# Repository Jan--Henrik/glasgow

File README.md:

# Glasgow Debug Tool

# This is not the official revC2 branch, I just added USB-C for myself!

**Want one? [Subscribe here](https://mailchi.mp/44980ff6f0ab/glasgow-announcements).**

**Let's chat! Our IRC channel is [#glasgow at freenode.net](https://webchat.freenode.net/?channels=glasgow); our discussion forum is [glasgow.whitequark.org](https://glasgow.whitequark.org/).**

**Important note: if you are looking to assemble boards yourself, use only revC1.**

## What is Glasgow?

Glasgow is a tool for exploring digital interfaces, aimed at embedded developers, reverse engineers, digital archivists, electronics hobbyists, and everyone else who wants to communicate to a wide selection of digital devices with high reliability and minimum hassle. It can be attached to most devices without additional active or passive components, and includes extensive protection from unexpected conditions and operator error.

The Glasgow hardware can support many digital interfaces because it uses reconfigurable logic. Instead of only offering a small selection of standard hardware supported interfaces, it uses an FPGA to adapt on the fly to the task at hand without compromising on performance or reliability, even for unusual, custom or obsolete interfaces.

The Glasgow software is a set of building blocks designed to eliminate incidental complexity. Each interface is packaged into a self-contained *applet* that can be used directly from the command line, or reused as a part of a more complex system. Using Glasgow does not require any programming knowledge, although it becomes much more powerful if you know a bit of Python.

## What can I do with Glasgow?

Some of the tasks Glasgow can do well are:

  * communicate via UART,
    * automatically determine and follow the baud rate of device under test,
  * initiate transactions via SPI or I²C,
  * read and write 24-series EEPROMs,
  * read and write 25-series Flash memories,
    * determine memory parameters via SFDP,
  * read and write ONFI-compatible Flash memories,
    * determine memory parameters via ONFI parameter page,
  * program and verify AVR microcontrollers with SPI interface,
  * automatically determine unknown JTAG pinout,
  * play back JTAG SVF files,
  * debug ARC processors via JTAG,
  * debug some MIPS processors via EJTAG,
  * program and verify XC9500XL CPLDs via JTAG,
  * synthesize sound using a Yamaha OPLx/OPM chip and play it in real time on a webpage,
  * read raw modulated data from 5.25"/3.5" floppy drives,
  * ... and more!

Everything above can be done with only a Glasgow revC board, some wires, and depending on the device under test, external power.

## How does using Glasgow look like?

Watch a typical command-line workflow in this screencast:

## What hardware does Glasgow use?

The Glasgow hardware evolves over time, with each major milestone called a "revision". Although all revisions are, and will always be supported with the same software, they vary significantly in their capabilities, and the chosen revision will limit the possible tasks.

Glasgow boards use a version in the `revXN` format, where `X` is a revision letter (increased on major design changes) and `N` is a stepping number (increased on any layout or component changes). For example, `revC0` is the first stepping of revision C.

### revA/revB

Revisions A and B have not been produced in significant amounts, contain major design issues, and are therefore mostly of historical interest. Nevertheless, everyone who has one of the revA/revB boards can keep using them—forever.

### revC

Revision C is the latest revision and is being prepared for mass production. It provides 16 I/O pins with a maximum frequency of approx. 100 MHz\*, independent direction control and independent programmable pull-up/pull-down resistors. The I/O pins are grouped into two I/O ports that can use any voltage from 1.8 V to 5 V, sense and monitor I/O voltage of the device under test, as well as provide up to 150 mA of power. The board uses USB 2 for power, configuration, and communication, achieving up to 336 Mbps (42 MB/s) of sustained combined throughput.

<sub>\* Maximum frequency achievable in practice depends on many factors and will vary greatly with specific interface and applet design. 24 MHz non-DDR can be achieved for most interfaces with minimal effort.</sub>

## What software does Glasgow use?

Glasgow is written entirely in Python 3. The interface logic that runs on the FPGA is described using [Migen](https://m-labs.hk/migen/), which is a Python-based domain specific language. The supporting code that runs on the host PC is written in Python with [asyncio](https://docs.python.org/3/library/asyncio.html). This way, the logic on the FPGA can be assembled on demand for any requested configuration, keeping it as fast and compact as possible, and code can be shared between gateware and software, removing the need to add error-prone "glue" boilerplate.

Glasgow would not be possible without the [open-source iCE40 FPGA toolchain](http://www.clifford.at/icestorm/), which is not only very reliable but also extremely fast. It is so fast that FPGA bitstreams are not cached (beyond not rebuilding the bitstream already on the device), as it only takes a few seconds to build one from scratch for something like an UART. When developing a new applet it is rarely necessary to wait for the toolchain.

Implementing reliable, high-performance USB communication is not trivial—packetization, buffering, and USB quirks add up. Glasgow abstracts away USB: on the FPGA, the applet gateware writes to or reads from a FIFO, and on the host, applet software writes to or reads from a socket-like interface. Idiomatic Python code can communicate at maximum USB 2 bulk bandwidth on a modern PC without additional effort. Moreover, when a future Glasgow revision will use Ethernet in addition to USB, no changes to applet code will be required.

Debugging new applets can be hard, especially if bidirectional buses are involved. Glasgow provides a built-in cycle-accurate logic analyzer that can relate the I/O pin level and direction changes to commands and responses received and sent by the applet. The logic analyzer compresses waveforms and can pause the applet if its buffer is about to overflow.

## How do I use Glasgow?

### ... with Linux?

**Multiple people have reported various issues with the installation instructions below. If any part of these does not work, please file it as a bug, so that the experience can be made more smooth for everyone.**

You will need git, build tools, sdcc, Python 3.7 (or a newer version, in which case replace `3.7` with that version below). On a Debian or Ubuntu system these can be installed with:

    apt-get install --no-install-recommends git build-essential sdcc \
      python3.7 python3-setuptools python3-libusb1 python3-aiohttp python3-bitarray python3-crcmod

You will also need Yosys and nextpnr-ice40, both from the master branch. Follow the setup instructions for [Yosys](https://github.com/yosysHQ/yosys/#setup) and [nextpnr](https://github.com/YosysHQ/nextpnr/#nextpnr-ice40).

Obtain the source code:

    git clone https://github.com/GlasgowEmbedded/glasgow
    cd glasgow
    git submodule update --init vendor/libfx2

Configure your system to allow unprivileged access (for anyone in the `plugdev` group) to the Glasgow hardware:

    sudo cp config/99-glasgow.rules /etc/udev/rules.d

Install the dependencies and the binaries for the current user:

    cd software
    python3.7 setup.py develop --user

The binaries are placed in `$HOME/.local/bin`, so be sure to add that directory to the `PATH` environment variable; after this, you can run `glasgow` from a terminal. Instead of adjusting `PATH` it is also possible to use `python3.7 -m glasgow.cli`.

When you connect your board for the first time after assembly you have to flash it initially, run the following command.

    glasgow factory --rev {A0|B0|C0|C1}

To update the source code, do:

    cd glasgow
    git pull
    cd software
    python3.7 setup.py build_ext

### ... with Windows?

Although first-class Windows support is an important goal and Glasgow already works on Windows, the installation process is not yet ready.

## Who made Glasgow?

  * [@whitequark](https://github.com/whitequark) came up with the design, coordinates the project and implements most of gateware and software;
  * [@awygle](https://github.com/awygle) designed the power/analog port circuitry and helped with layout of revB;
  * [@marcan](https://github.com/marcan) improved almost every aspect of hardware for revC;
  * [@esden](https://github.com/esden) is handling batch manufacturing;
  * [@smunaut](https://github.com/smunaut) provided advice crucial for stability and performance of USB communication;
  * [@electronic_eel](https://github.com/electronic_eel) designed the test jig and advanced protection circuitry;
  * ... and many [other people](https://github.com/GlasgowEmbedded/Glasgow/graphs/contributors).

## License

Glasgow is distributed under the terms of both 0-clause BSD license as well as Apache 2.0 license.

See [LICENSE-0BSD](LICENSE-0BSD.txt) and [LICENSE-Apache-2.0.txt](LICENSE-Apache-2.0.txt) for details.

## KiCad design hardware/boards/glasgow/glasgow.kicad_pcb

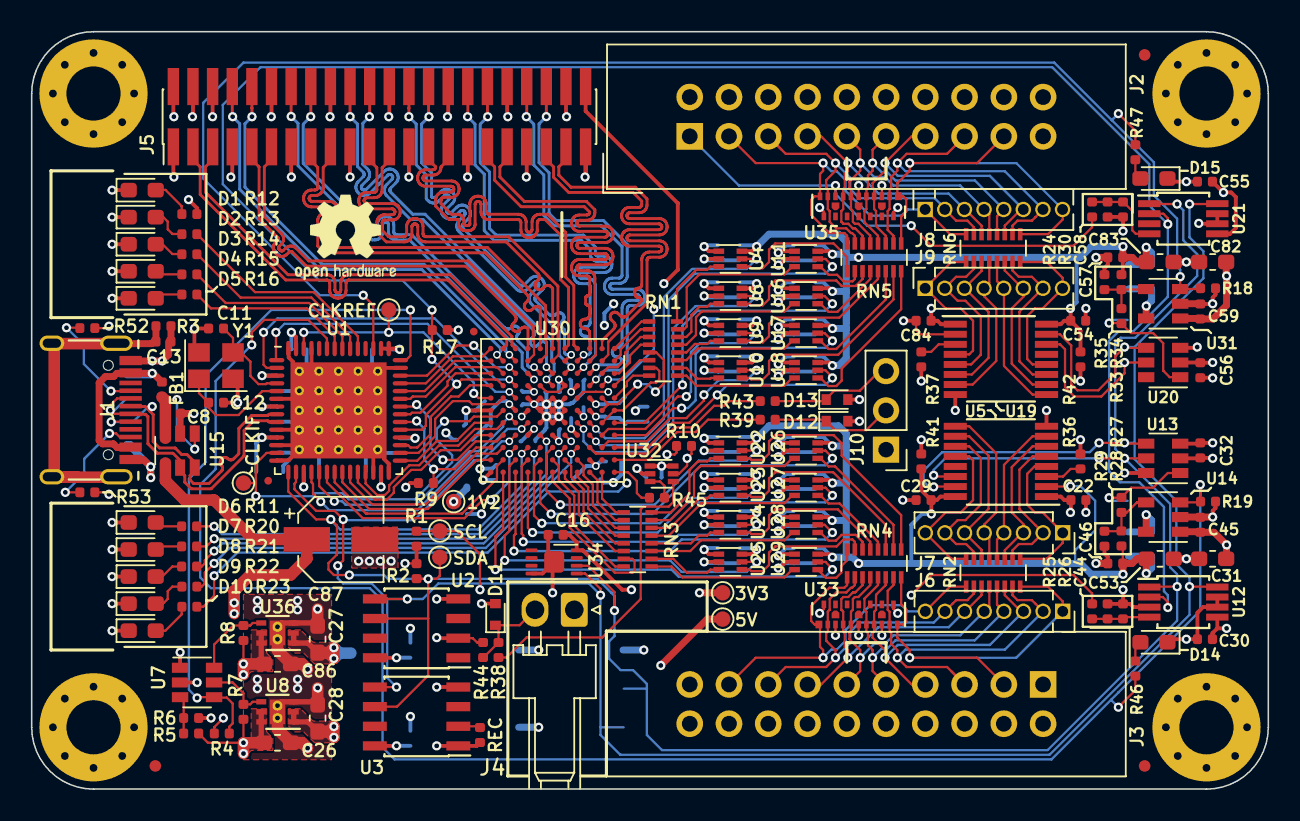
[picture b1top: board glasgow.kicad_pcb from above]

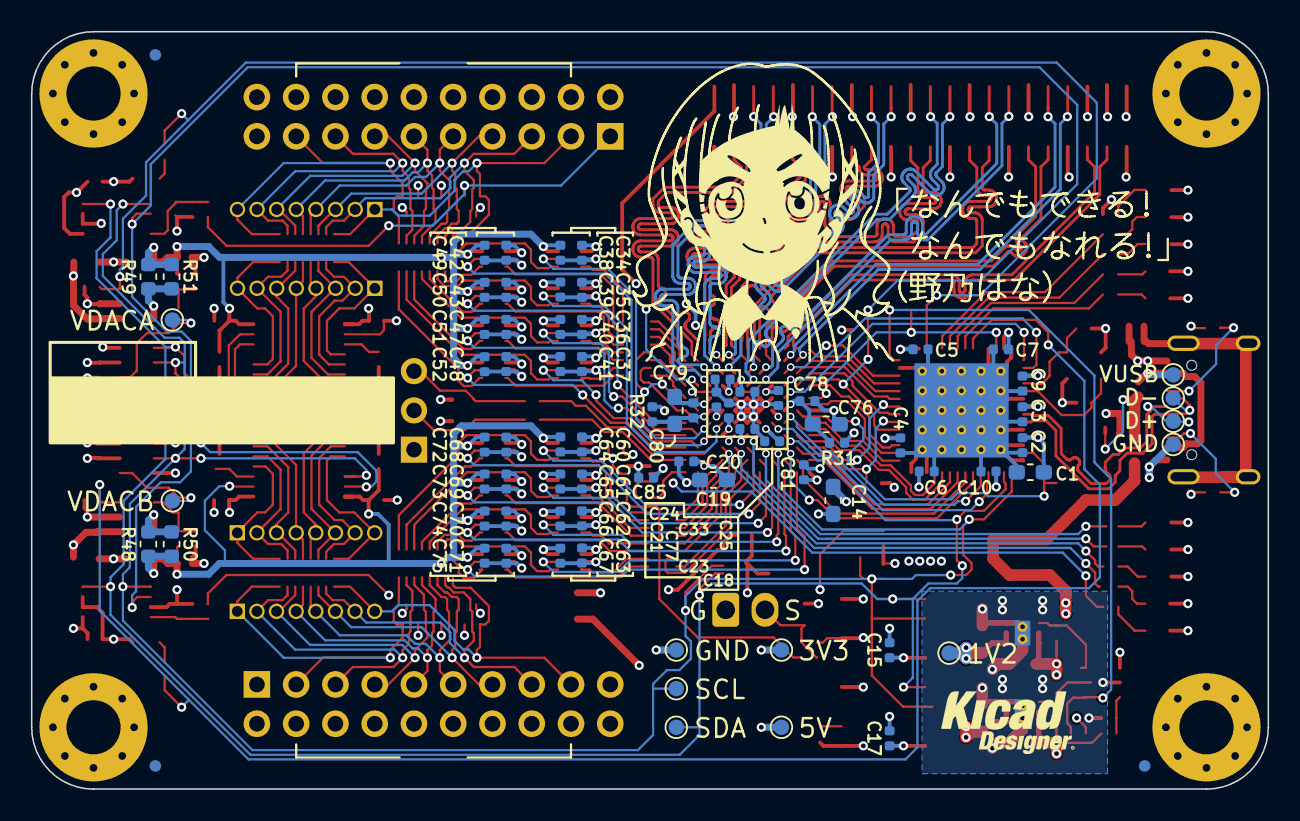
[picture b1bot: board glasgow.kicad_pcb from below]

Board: 4 copper layers, 80.0 x 49.0 mm, 241 parts (81 on the bottom side), 216 nets.

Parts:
C1, C14, C19, C26, C27, C28, C31, C53, C76, C80, C82, C83, C86: 4u7; C_0603_1608Metric_Pad1.05x0.95mm_HandSolder
C2, C3, C4, C5, C6, C7, C8, C9, C10, C13, C15, C16, C17, C18, C20, C21, C22, C23, C24, C25, C29, C30, C32, C33, C34, C35, C36, C37, C38, C39, C40, C41, C42, C43, C45, C46, C47, C48, C49, C50, C51, C52, C54, C55, C56, C57, C59, C60, C61, C62, C63, C64, C65, C66, C67, C68, C69, C70, C71, C72, C73, C74, C75, C77, C78, C79, C81, C84, C85: u1; C_0402_1005Metric
C11, C12: 18p; C_0402_1005Metric
C44, C58: 12n; C_0402_1005Metric
C87: 150u; CP_Elec_5x3.9
D1, D2, D3, D14, D15: GRN; LED_0603_1608Metric_Pad1.05x0.95mm_HandSolder
D4: YEL; LED_0603_1608Metric_Pad1.05x0.95mm_HandSolder
D5: RED; LED_0603_1608Metric_Pad1.05x0.95mm_HandSolder
D6, D10: BLU; LED_0603_1608Metric_Pad1.05x0.95mm_HandSolder
D7, D9: PNK; LED_0603_1608Metric_Pad1.05x0.95mm_HandSolder
D8: WHT; LED_0603_1608Metric_Pad1.05x0.95mm_HandSolder
D11, D12, D13: ESD5Z5.0T1G; D_SOD-523
FB1: Ferrite_Bead; L_0402_1005Metric
FID1, FID2, FID3, FID4, FID5, FID6: Fiducial_0.75mm_Dia_1.5mm_Outer
FID7, FID8: Fiducial_0.5mm_Dia_1mm_Outer
J1: USB; USB-C 16Pin
J2, J3: Conn_02x10_Odd_Even; IDC-Header_2x10_P2.54mm_Vertical
J4: Conn_01x02; Molex_KK-254_1x02_P2.54mm_Horizontal
J5: Conn_02x22_Odd_Even; PinHeader_2x22_P1.27mm_Vertical_SMD
J6, J7, J8, J9: Conn_01x08; PinSocket_1x08_P1.27mm_Vertical
J10: Conn_01x03; PinHeader_1x03_P2.54mm_Vertical
MK1, MK2, MK3, MK4: Mounting_Hole_PAD; MountingHole_3.5mm_Pad_Via_CrtYd
NONO_HANA: MECHOKKU; nono_hana
R1, R2, R15: 2k2; R_0402_1005Metric
R3, R4, R7, R8, R9, R17: 100k; R_0402_1005Metric
R5, R29, R35: 24k3; R_0402_1005Metric
R6, R16, R18, R19, R20, R22, R24, R25, R26, R30, R36, R37, R44: 10k; R_0402_1005Metric
R10, R41, R42: 1k; R_0402_1005Metric
R11, R23: 4k7; R_0402_1005Metric
R12, R13, R14, R46, R47: 20k; R_0402_1005Metric
R21: 6k8; R_0402_1005Metric
R27, R33: 49k9; R_0402_1005Metric
R28, R34: 59k; R_0402_1005Metric
R31, R32: 100; R_0402_1005Metric
R38, R39, R43, R45: 47; R_0402_1005Metric
R40: DNP; R_0402_1005Metric
R48, R49: 0.68; R_0603_1608Metric
R50, R51: DNP; R_0603_1608Metric
R52, R53: 5k1; R_0402_1005Metric
RN1, RN3, RN4, RN5: 33; R_Array_Convex_8x0602
RN2, RN6: 10k; R_Array_Convex_8x0602
TP1, TP8: 5V; TestPoint_Pad_D1.0mm
TP2, TP17: 1V2; TestPoint_Pad_D1.0mm
TP3, TP7, TP9: 3V3; TestPoint_Pad_D1.0mm
TP4, TP10: SDA; TestPoint_Pad_D1.0mm
TP5, TP11: SCL; TestPoint_Pad_D1.0mm
TP6: CLKREF; TestPoint_Pad_D1.0mm
TP12: GND; TestPoint_Pad_D1.0mm
TP13: VBUS; TestPoint_Pad_D1.0mm
TP14: USBGND; TestPoint_Pad_D1.0mm
TP15: USBDP; TestPoint_Pad_D1.0mm
TP16: USBDM; TestPoint_Pad_D1.0mm
TP18, TP19: VDAC; TestPoint_Pad_D1.0mm
U1: CY7C68013A-56LTX; Cypress_QFN-56-1EP_8x8mm_P0.5mm_EP6.22x6.22mm_ThermalVias
U2: CAT24M01W; SOIC-8_3.9x4.9mm_P1.27mm
U3: CAT24C256W; SOIC-8_3.9x4.9mm_P1.27mm
U4, U6, U9, U10, U11, U16, U17, U18, U22, U23, U24, U25, U26, U27, U28, U29, U32: SN74LVC1T45DRL; SOT-563
U5, U19: PCA6408APW; TSSOP-16_4.4x5mm_P0.65mm
U7: LM3880MF-1AF; SOT-23-6
U8: TLV75533PDRVR; DFN-6-1EP_2x2mm_P0.65mm_EP1x1.6mm_ThermalVias
U12, U21: ADC081C021CIMM; MSOP-8_3x3mm_P0.65mm
U13, U20: DAC081C081CIMK; SOT-23-6
U14, U31: TPS73101DBV; SOT-23-5
U15: TPD3S014; SOT-23-6
U30: ICE40HX8K-BG121; BGA-121_9.0x9.0mm_Layout11x11_P0.8mm_Ball0.4mm_Pad0.35mm_NS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
U33, U35: MG2040; UDFN-18-3EP_5.5x1.5mm_P0.5mm_EP0.5x0.5mm
U34: ATECC508A; WDFN-8-1EP_3x2mm_P0.5mm_EP1.3x1.4mm
U36: TLV73312PQDRVRQ1; DFN-6-1EP_2x2mm_P0.65mm_EP1x1.6mm_ThermalVias
Y1: 24M; Crystal_SMD_3225-4Pin_3.2x2.5mm

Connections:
+1V2: C14.1, C18.1, C24.1, C25.1, C27.1, C77.1, R31.2, R32.2, TP2.1, TP17.1, U30.D4, U30.D8, U30.H4, U30.H8, U36.1, U36.2
+3V3: C1.1, C2.1, C3.1, C4.1, C5.1, C6.1, C7.1, C9.1, C10.1, C15.1, C16.1, C17.1, C19.1, C20.1, C21.1, C22.1, C23.1, C28.1, C30.1, C32.1, C34.1, C35.1, C36.1, C37.1, C42.1, C43.1, C47.1, C48.1, C55.1, C56.1, C60.1, C61.1, C62.1, C63.1, C68.1, C69.1, C70.1, C71.1, C81.1, C84.1, C85.1, J5.2, R1.2, R2.2, R4.2, R12.1, R17.2, R36.2, R37.2, R40.2, R44.2, TP3.1, TP9.1, U1.3, U1.7, U1.11, U1.17, U1.27, U1.32, U1.43, U1.44, U1.55, U2.2, U2.8, U3.1, U3.8, U4.1, U5.1, U6.1, U8.1, U8.2, U9.1, U10.1, U11.1, U12.5, U13.2, U16.1, U17.1, U18.1, U19.1, U20.2, U21.5, U22.1, U23.1, U24.1, U25.1, U26.1, U27.1, U28.1, U29.1, U30.C10, U30.D6, U30.F8, U30.H6, U30.L11, U32.1, U32.6, U34.8
+5V: C26.2, C31.1, C45.1, C59.1, C82.1, C86.2, C87.1, R5.2, R7.2, R8.2, TP1.1, TP8.1, U7.1, U8.5, U8.6, U14.1, U15.4, U31.1, U36.5, U36.6
/1V2EN: R8.1, U7.6, U36.4
/3V3EN: R7.1, U7.5, U8.4
/A0: U1.37, U30.K3
/A1: U1.38, U30.L2
/CLKIF: TP7.1, U1.13, U30.K6
/CLKREF: TP6.1, U1.54, U30.D5, U30.L5
/D0: U1.18, U30.H7
/D1: U1.19, U30.J7
/D2: U1.20, U30.J9
/D3: U1.21, U30.K10
/D4: U1.22, U30.L10
/D5: U1.23, U30.K9
/D6: U1.24, U30.L8
/D7: U1.25, U30.K7
/ENVA: R18.1, R47.1, U1.45, U31.3
/ENVB: R19.1, R46.1, U1.51, U14.3
/FLAGA: U1.29, U30.L7
/FLAGB: U1.30, U30.K5
/FLAGC: U1.31, U30.L4
/FLAGD: U1.40, U30.J3
/FPGA_DONE: U1.36, U30.K8
/GNDPLL0: C76.2, C78.2, U30.L6
/GNDPLL1: C79.2, C80.2, U30.C5
/IO_Banks/DA0: U4.5, U30.C7
/IO_Banks/DA1: U11.5, U30.C8
/IO_Banks/DA2: U6.5, U30.D7
/IO_Banks/DA3: U16.5, U30.A7
/IO_Banks/DA4: U9.5, U30.B8
/IO_Banks/DA5: U17.5, U30.A8
/IO_Banks/DA6: U10.5, U30.B9
/IO_Banks/DA7: U18.5, U30.A9
/IO_Banks/DB0: U22.5, U30.F9
/IO_Banks/DB1: U26.5, U30.G11
/IO_Banks/DB2: U23.5, U30.G10
/IO_Banks/DB3: U27.5, U30.H11
/IO_Banks/DB4: U24.5, U30.H10
/IO_Banks/DB5: U28.5, U30.J11
/IO_Banks/DB6: U25.5, U30.J10
/IO_Banks/DB7: U29.5, U30.K11
/IO_Banks/IO_Buffer_A/VFB: R33.2, R34.1, R35.2, U31.4
/IO_Banks/IO_Buffer_A/VSAMP: C58.1, R24.1, R30.2, U21.4
/IO_Banks/IO_Buffer_A/VSENSE: J2.1, R24.2, U35.9
/IO_Banks/IO_Buffer_A/Y0: RN5.1, U4.4
/IO_Banks/IO_Buffer_A/Y1: RN5.2, U11.4
/IO_Banks/IO_Buffer_A/Y2: RN5.3, U6.4
/IO_Banks/IO_Buffer_A/Y3: RN5.4, U16.4
/IO_Banks/IO_Buffer_A/Y4: RN5.5, U9.4
/IO_Banks/IO_Buffer_A/Y5: RN5.6, U17.4
/IO_Banks/IO_Buffer_A/Y6: RN5.7, U10.4
/IO_Banks/IO_Buffer_A/Y7: RN5.8, U18.4
/IO_Banks/IO_Buffer_A/Z0: J2.3, J8.1, RN5.16, RN6.8, U35.11
/IO_Banks/IO_Buffer_A/Z1: J2.5, J8.2, RN5.15, RN6.7, U35.10
/IO_Banks/IO_Buffer_A/Z2: J2.7, J8.3, RN5.14, RN6.6, U35.8
/IO_Banks/IO_Buffer_A/Z3: J2.9, J8.4, RN5.13, RN6.5, U35.7
/IO_Banks/IO_Buffer_A/Z4: J2.11, J8.5, RN5.12, RN6.4, U35.5
/IO_Banks/IO_Buffer_A/Z5: J2.13, J8.6, RN5.11, RN6.3, U35.4
/IO_Banks/IO_Buffer_A/Z6: J2.15, J8.7, RN5.10, RN6.2, U35.2
/IO_Banks/IO_Buffer_A/Z7: J2.17, J8.8, RN5.9, RN6.1, U35.1
/IO_Banks/IO_Buffer_B/VFB: R27.2, R28.1, R29.2, U14.4
/IO_Banks/IO_Buffer_B/VSAMP: C44.1, R25.1, R26.2, U12.4
/IO_Banks/IO_Buffer_B/VSENSE: J3.1, R25.2, U33.9
/IO_Banks/IO_Buffer_B/Y0: RN4.1, U22.4
/IO_Banks/IO_Buffer_B/Y1: RN4.2, U26.4
/IO_Banks/IO_Buffer_B/Y2: RN4.3, U23.4
/IO_Banks/IO_Buffer_B/Y3: RN4.4, U27.4
/IO_Banks/IO_Buffer_B/Y4: RN4.5, U24.4
/IO_Banks/IO_Buffer_B/Y5: RN4.6, U28.4
/IO_Banks/IO_Buffer_B/Y6: RN4.7, U25.4
/IO_Banks/IO_Buffer_B/Y7: RN4.8, U29.4
/IO_Banks/IO_Buffer_B/Z0: J3.3, J6.1, RN2.8, RN4.16, U33.11
/IO_Banks/IO_Buffer_B/Z1: J3.5, J6.2, RN2.7, RN4.15, U33.10
/IO_Banks/IO_Buffer_B/Z2: J3.7, J6.3, RN2.6, RN4.14, U33.8
/IO_Banks/IO_Buffer_B/Z3: J3.9, J6.4, RN2.5, RN4.13, U33.7
/IO_Banks/IO_Buffer_B/Z4: J3.11, J6.5, RN2.4, RN4.12, U33.5
/IO_Banks/IO_Buffer_B/Z5: J3.13, J6.6, RN2.3, RN4.11, U33.4
/IO_Banks/IO_Buffer_B/Z6: J3.15, J6.7, RN2.2, RN4.10, U33.2
/IO_Banks/IO_Buffer_B/Z7: J3.17, J6.8, RN2.1, RN4.9, U33.1
/IO_Banks/QA0: RN1.1, U30.A1
/IO_Banks/QA1: RN1.2, U30.A2
/IO_Banks/QA2: RN1.3, U30.B3
/IO_Banks/QA3: RN1.4, U30.A3
/IO_Banks/QA4: RN1.5, U30.B5, U30.B6
/IO_Banks/QA5: RN1.6, U30.A4
/IO_Banks/QA6: RN1.7, U30.A6, U30.B7
/IO_Banks/QA7: RN1.8, U30.A5
/IO_Banks/QB0: RN3.1, U30.B11
/IO_Banks/QB1: RN3.2, U30.C11
/IO_Banks/QB2: RN3.3, U30.D10
/IO_Banks/QB3: RN3.4, U30.D11
/IO_Banks/QB4: RN3.5, U30.E10
/IO_Banks/QB5: RN3.6, U30.E11
/IO_Banks/QB6: RN3.7, U30.F11
/IO_Banks/QB7: RN3.8, U30.F10
/IO_Banks/U1: R11.1, U30.G9
/IO_Banks/U2: R20.1, U30.G8
/IO_Banks/U3: R21.1, U30.E9
/IO_Banks/U4: R22.1, U30.D9
/IO_Banks/U5: R23.1, U30.E8
/IO_Banks/VIOA: C38.1, C39.1, C40.1, C41.1, C49.1, C50.1, C51.1, C52.1, C54.1, C57.1, C83.1, J2.2, R34.2, R42.2, R49.2, R51.2, U4.6, U6.6, U9.6, U10.6, U11.6, U16.6, U17.6, U18.6, U19.16, U35.3, U35.6
/IO_Banks/VIOB: C29.1, C46.1, C53.1, C64.1, C65.1, C66.1, C67.1, C72.1, C73.1, C74.1, C75.1, J3.2, R28.2, R41.2, R48.2, R50.2, U5.2, U5.16, U22.6, U23.6, U24.6, U25.6, U26.6, U27.6, U28.6, U29.6, U33.3, U33.6
/IO_Banks/VIO_AUX: C33.1, J5.44, U30.E4, U30.G4
/IO_Banks/Z0_N: J5.41, U30.B2
/IO_Banks/Z0_P: J5.39, U30.B1
/IO_Banks/Z1_N: J5.38, U30.C3
/IO_Banks/Z1_P: J5.40, U30.C4
/IO_Banks/Z2_N: J5.33, U30.C1
/IO_Banks/Z2_P: J5.35, U30.C2
/IO_Banks/Z3_N: J5.29, U30.D1
/IO_Banks/Z3_P: J5.27, U30.E1
/IO_Banks/Z4_N: J5.34, U30.D3
/IO_Banks/Z4_P: J5.32, U30.D2
/IO_Banks/Z5_N: J5.26, U30.E3
/IO_Banks/Z5_P: J5.28, U30.E2
/IO_Banks/Z6_N: J5.23, U30.F2
/IO_Banks/Z6_P: J5.21, U30.F1
/IO_Banks/Z7_N: J5.20, U30.F3
/IO_Banks/Z7_P: J5.22, U30.F4
/IO_Banks/Z8_N: J5.17, U30.G2
/IO_Banks/Z8_P: J5.15, U30.G1
/IO_Banks/Z9_N: J5.14, U30.H3
/IO_Banks/Z9_P: J5.16, U30.G3
/IO_Banks/Z10_N: J5.11, U30.H2
/IO_Banks/Z10_P: J5.9, U30.H1
/IO_Banks/Z11_N: J5.3, U30.K1
/IO_Banks/Z11_P: J5.5, U30.J1
/IO_Banks/Z12_N: J5.10, U30.J2
/IO_Banks/Z12_P: J5.8, U30.K2
/IO_Banks/~SYNC: D11.1, J4.2, R38.1, R44.1
/LED_ACT: R15.1, U1.49
/LED_CY: R13.1, U1.47
/LED_ERR: R16.1, U1.50
/LED_FPGA: R14.1, U1.48
/OE: U1.35, U30.L3
/PGOOD: R5.1, R6.2, U7.3
/PKTEND: U1.39, U30.L1
/RD: U1.1, U30.J5
/SCL: R2.1, TP5.1, TP11.1, U1.15, U2.6, U3.6, U5.14, U12.1, U13.5, U19.14, U20.5, U21.1, U30.H9, U34.6
/SDA: R1.1, TP4.1, TP10.1, U1.16, U2.5, U3.5, U5.15, U12.8, U13.4, U19.15, U20.4, U21.8, U30.J8, U34.5
/SHLD: C13.1, J1.S1, R3.1
/USB_N: J1.A7, J1.B7, TP16.1, U1.9, U15.5
/USB_P: J1.A6, J1.B6, TP15.1, U1.8, U15.6
/VCCPLL0: C76.1, C78.1, R31.1, U30.J6
/VCCPLL1: C79.1, C80.1, R32.1, U30.C6
/VUSB: C8.1, FB1.2, U15.1, U15.3
/WR: U1.2, U30.J4
/XTALIN: C12.1, U1.5, Y1.1
/XTALOUT: C11.1, U1.4, Y1.3
/~ALERT: R17.1, U1.33, U12.2, U21.2, U30.K4
/~CY_RESET: R4.1, U1.42, U7.4
/~FPGA_RESET: R9.2, U1.34, U30.L9
GND: C1.2, C2.2, C3.2, C4.2, C5.2, C6.2, C7.2, C8.2, C9.2, C10.2, C11.2, C12.2, C13.2, C14.2, C15.2, C16.2, C17.2, C18.2, C19.2, C20.2, C21.2, C22.2, C23.2, C24.2, C25.2, C26.1, C27.2, C28.2, C29.2, C30.2, C31.2, C32.2, C33.2, C34.2, C35.2, C36.2, C37.2, C38.2, C39.2, C40.2, C41.2, C42.2, C43.2, C44.2, C45.2, C46.2, C47.2, C48.2, C49.2, C50.2, C51.2, C52.2, C53.2, C54.2, C55.2, C56.2, C57.2, C58.2, C59.2, C60.2, C61.2, C62.2, C63.2, C64.2, C65.2, C66.2, C67.2, C68.2, C69.2, C70.2, C71.2, C72.2, C73.2, C74.2, C75.2, C77.2, C81.2, C82.2, C83.2, C84.2, C85.2, C86.1, C87.2, D1.1, D2.1, D3.1, D4.1, D5.1, D6.1, D7.1, D8.1, D9.1, D10.1, D11.2, D12.2, D13.2, D14.1, D15.1, J1.A1, J1.A12, J1.B1, J1.B12, J2.4, J2.6, J2.8, J2.10, J2.12, J2.14, J2.16, J2.18, J3.4, J3.6, J3.8, J3.10, J3.12, J3.14, J3.16, J3.18, J4.1, J5.1, J5.4, J5.6, J5.7, J5.12, J5.13, J5.18, J5.19, J5.24, J5.25, J5.30, J5.31, J5.36, J5.37, J5.42, J5.43, J10.1, MK1.1, MK2.1, MK3.1, MK4.1, R3.2, R6.1, R9.1, R10.2, R18.2, R19.2, R26.1, R29.1, R30.1, R35.1, R41.1, R42.1, R52.1, R53.1, TP12.1, TP14.1, U1.6, U1.10, U1.12, U1.14, U1.26, U1.28, U1.41, U1.53, U1.56, U1.57, U2.4, U3.4, U4.2, U5.8, U6.2, U7.2, U8.3, U8.7, U9.2, U10.2, U11.2, U12.3, U12.6, U12.7, U13.3, U13.6, U14.2, U15.2, U16.2, U17.2, U18.2, U19.2, U19.8, U20.3, U21.6, U21.7, U22.2, U23.2, U24.2, U25.2, U26.2, U27.2, U28.2, U29.2, U30.E5, U30.E6, U30.E7, U30.F5, U30.F6, U30.F7, U30.G5, U30.G6, U30.G7, U30.H5, U31.2, U32.2, U33.12, U33.18, U34.4, U34.9, U35.12, U35.18, U36.3, U36.7, Y1.2, Y1.4
unnamed: D1.2, R12.2
unnamed: D2.2, R13.2
unnamed: D3.2, R14.2
unnamed: D4.2, R15.2
unnamed: D5.2, R16.2
unnamed: D6.2, R11.2
unnamed: D7.2, R20.2
unnamed: D8.2, R21.2
unnamed: D9.2, R22.2
unnamed: D10.2, R23.2
unnamed: D12.1, J10.2, R39.1
unnamed: D13.1, J10.3, R43.1
unnamed: D14.2, R46.2
unnamed: D15.2, R47.2
unnamed: FB1.1, J1.A4, J1.A9, J1.B4, J1.B9, TP13.1
unnamed: J1.A5, R52.2
unnamed: J1.B5, R53.2
unnamed: J7.1, RN2.9, U5.4
unnamed: J7.2, RN2.10, U5.5
unnamed: J7.3, RN2.11, U5.6
unnamed: J7.4, RN2.12, U5.7
unnamed: J7.5, RN2.13, U5.9
unnamed: J7.6, RN2.14, U5.10
unnamed: J7.7, RN2.15, U5.11
unnamed: J7.8, RN2.16, U5.12
unnamed: J9.1, RN6.9, U19.4
unnamed: J9.2, RN6.10, U19.5
unnamed: J9.3, RN6.11, U19.6
unnamed: J9.4, RN6.12, U19.7
unnamed: J9.5, RN6.13, U19.9
unnamed: J9.6, RN6.14, U19.10
unnamed: J9.7, RN6.15, U19.11
unnamed: J9.8, RN6.16, U19.12
unnamed: R10.1, U30.B4, U32.5
unnamed: R27.1, TP18.1, U13.1
unnamed: R33.1, TP19.1, U20.1
unnamed: R36.1, U5.3
unnamed: R37.1, U19.3
unnamed: R38.2, U32.4
unnamed: R39.2, U30.A10
unnamed: R40.1, U3.2
unnamed: R43.2, U30.C9
unnamed: R45.1, U32.3
unnamed: R45.2, U30.A11
unnamed: R48.1, R50.1, U14.5
unnamed: R49.1, R51.1, U31.5
unnamed: RN1.9, U18.3
unnamed: RN1.10, U10.3
unnamed: RN1.11, U17.3
unnamed: RN1.12, U9.3
unnamed: RN1.13, U16.3
unnamed: RN1.14, U6.3
unnamed: RN1.15, U11.3
unnamed: RN1.16, U4.3
unnamed: RN3.9, U29.3
unnamed: RN3.10, U25.3
unnamed: RN3.11, U28.3
unnamed: RN3.12, U24.3
unnamed: RN3.13, U27.3
unnamed: RN3.14, U23.3
unnamed: RN3.15, U26.3
unnamed: RN3.16, U22.3

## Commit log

2020-01-08 revC2: added output files
2020-03-17 added revC1 otter edition gerber
